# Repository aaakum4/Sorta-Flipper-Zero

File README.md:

# Sorta-Flipper-Zero by aaakum4 (Jake)

At the cost of a flipper zero, I thought that I may never own one. Then I found a hackster.io page that went through a full DIY and cheap Flipper Zero and I thought I'd try it myself with some changes. With this project, I should also learn a ton about PCB's and how electronics work.

V1 is a modular based project to ensure that it will work as planned, then, , I will completely custom make it for V2. 

Features: 
- Bluetooth Low Energy (BLE)
- Sub-GHz RF support (433 MHz)
- NFC / RFID functionality
- Infrared (IR) transmit and receive
- On-device display
- Physical navigation and action buttons
- Audible feedback via buzzer
- MicroSD card storage
- USB-C connectivity
- External antenna support

Not included (compared to a standard Flipper): 
- iButton / 1-Wire support - Capacitive touch input
- Internal battery charging and management
- Integrated antennas
- Fully enclosed, consumer-ready housing (I will make one for v2)

## Step 1 - Looking at the Flipper Zero Hardware

Before starting this project, I went through the Flipper Zero hardware documentation to understand how the device is built and what components it uses.

https://docs.flipper.net/zero/development/hardware/tech-specs
https://docs.flipper.net/zero/development/hardware/schematic

From this, I created the table below listing the main hardware blocks used in the Flipper Zero.
This table is used as a reference to understand the system, not something to copy directly.

### Flipper Zero – Hardware Component Overview

### Simplifying the Design (v1)
To keep the first version realistic and achievable, a few things were intentionally simplified.

#### USB Power Only
The device is powered only through USB, with no internal rechargeable battery.
This removes a lot of complexity around battery charging and safety, and makes early testing much easier. Portability isn’t the focus for the first version.

#### BLE Using a Module or Dev Board
Instead of designing a full BLE RF circuit, this project uses either an STM32WB5MMG module or a NUCLEO-WB55RG during early development.
This avoids antenna tuning issues and lets me focus more on firmware and overall system behaviour.

#### Simpler Sub-1 GHz Antenna
The Flipper Zero uses an antenna multiplexer to optimise different Sub-1 GHz bands. For this project, that part is left out.
A single antenna is used instead, which means reduced range, but much simpler hardware and easier bring-up.

#### Physical Reset Button
Rather than copying the Flipper Zero’s reset button combination logic, this design uses a dedicated reset button.
This keeps the schematic simpler and is more practical while debugging.

## Step 2 - v1 Hardware Selection (Module Based)
Based on the Flipper Zero reference design and the simplifications outlined above, the following components were chosen for the v1 module-based prototype.
This list reflects what will actually be used in the first working version of the project.

V1 - Selected Components:

## Step 3 – Schematic Design

With the overall architecture defined, I moved on to creating the full schematic in KiCad. The goal at this stage was to produce a complete, electrically correct design that could realistically be turned into a PCB, while still keeping the project modular and easy to iterate on.

I started by placing the STM32WB5MMGH6TR module and wiring all required power pins according to ST’s reference designs. This included separating the digital and analog supplies, tying VREF+ to VDDA, and correctly handling VBAT and VDDUSB. Decoupling capacitors were added close to each supply pin to ensure stable operation.

Next, the power system was designed around USB-C input. A main 3.3 V rail powers the MCU and core logic, while a second 3.3 V rail is used for external peripherals. 

Peripheral interfaces were then added. Instead of hard-coding specific modules, generic headers were used for NFC, Sub-1 GHz RF, display, IR, vibration, and expansion. These headers are labeled to match common module pinouts, allowing different breakout boards to be tested without changing the core design. Shared buses like SPI were carefully routed with separate chip-select signals.

Finally, the schematic was cleaned up and checked for electrical correctness. ERC warnings were addressed, unused pins were left intentionally for future use, and the design was reviewed to ensure it matched the original goals of being practical, modular, and suitable for a first hardware revision.

This step, to be honest, was kinda cooked. I went in a bit over my head with this and it took wayyyy longer than I had hoped and probably needed.

## Step 4 - Schematic fixes and cleanup

After the initial schematic was complete, I spent time going back through it to fix a number of electrical and structural issues flagged by ERC. This step was mainly about correcting mistakes rather than adding new features.

Most of the changes were around power domains, making sure VDD, VDDA, VREF+, VBAT, and VDDUSB were connected correctly and matched the STM32WB module datasheet. I cleaned up grounding, added and adjusted local decoupling capacitors, and removed a few incorrect connections that were previously masking ERC errors instead of solving them properly.

I also fixed the Bluetooth RF path, reworking the RF_OUT pin so it is routed through a DC-blocking capacitor to a u.FL connector. This replaces earlier incorrect handling of the RF pin and makes the onboard BLE functionality usable while keeping the design clean and standards-compliant.

This is an amazing sight, no ERC errors 🙏🏻

## Step 5 - Sorting and routing the board

I am now a new man...

This was my third time routing a PCB, and it was a mix of improvement… and pain. The Xiao MCU I used for the Macropad and the ESP32-S3-WROOM-1u for the development board don’t come close to the challenge I just faced. The STM32WB5MMG is tiny but packed with pins, making it a real test of patience. That said, I’m finally done, and I couldn’t be happier.

There were multiple reroutes along the way, mostly caused by pin congestion around the MCU and the sheer number of external connectors. Some compromises were necessary, like tighter clearances and smaller vias, but in the end, the board reached a fully routable and manufacturable state.

While it’s not perfect, this routing pass made me really proud of how far I’ve come since the Macropad project. It was a clear reminder that schematics are the easy part—routing is where designs are truly made or broken.

For this project, I worked with a 4-layer board (my first board over 2 layers) to manage density and RF performance, especially around the RF/Bluetooth section. I created a dedicated antenna keep-out zone to avoid copper interference, routed USB D+ and D− as a matched, parallel pair to maintain signal integrity, and widened power traces to 0.5 mm to reduce voltage drop.

Given the tight board size, I had to selectively use smaller vias and reduced trace widths in congested areas to complete the routing without violating design rules. To make assembly easier, I also added silkscreen boxes around each functional module, improving clarity and helping with placement. Looking back, having dedicated GND and +3.3 V layers definitely made this step much more manageable compared to what it would’ve been without them.

### The board

Size: 125mm x 70mm (quite alot bulkier than a normal flipper, I have no clue how they do it)
Vias:
1) Defult: 0.6 x 0.3
2) Smaller (Due to cramped space): 0.45 x 0.2
Routes:
1) Defult: Clearance = 0.2, Width = 0.2
2) Power: Clearance = 0.2, Width = 0.5
3) Smaller: Clearance = 0.2, Width = 0.15

#### Layer 1:

#### Layer 2: GND

#### Layer 3: +3V3

#### Layer 4:

#### 3D:

Estimated Time:
~2 hours of planning & component placement
~6 to 8 hours of routing + rerouting
~2 to 3 hours of cleanup, checks, and second-guessing everything

(Plus bonus time staring at the screen being stupid)

## Step ??? - Spontaneous Micro Project

For v2 of the Sorta Flipper Zero, I’ll most likely need to make a copper trace antenna for the NFC. For V1, I’m using a module, but I didn’t want to jump into V2 blindly. I decided to spend some time understanding how the module works, what I can bridge across, and even built my own small NFC card as an introduction to what I’ll need to do in V2.

Here’s the datasheet for the NFC module I hope to use: ST X-NUCLEO-NFC08A1

One thing I quickly noticed is that the antenna matters a lot. The orientation, size, and shape of the coil strongly affect the read range, and even small changes in trace layout or nearby copper can weaken the signal. This made it clear that designing a custom antenna will require careful attention.

I also learned that matching the antenna to the module is critical. The module expects the antenna to have roughly the right inductance; otherwise, communication becomes unreliable. Experimenting with the card showed me how adding or removing a turn in the coil noticeably changes performance.

Using the module is convenient because it handles much of the tuning internally. But seeing it in action made it obvious that if I want a custom copper trace for V2, I’ll need to account for these details myself.

This is the PCB I made from a simple schematic. I originally included an LED, but removed it in the PCB for the sake of readability and clarity. The file is in its own folder.

#### PCB:

#### 3D:

This step is not nesassary at all, but I truly found it really helpful with general understanding of this concept and I think it will be even more helpful when I make v2.

## Parts
Since alot of this iteration will be using modules there isn't that much soldering. Here is the parts list from JLCPCB PCBA.

## Firmware

Generating OTP Data (Flipper Zero)

This project uses the Flipper Zero firmware OTP generation script (scripts/otp.py) derived from the official Flipper Zero firmware repository (licensed under GPL-3.0) to generate device-specific OTP data.

### Example:

```
cd flipperzero-firmware/scripts

./otp.py generate \
  --version $((0x0c)) \
  --firmware $((0x07)) \
  --body $((0x09)) \
  --connect $((0x06)) \
  --display "mgg" \
  --color "transparent" \
  --region "world" \
  --name "Greg" \
  myotp
```

**Warning**: OTP memory is one-time programmable.
Flashing incorrect data may permanently affect the device.

### Installing Firmware via qFlipper

https://github.com/flipperdevices/qFlipper.git
Firmware installation is performed using qFlipper, the official Flipper Zero desktop application.

1. Install qFlipper from the official Flipper Zero website
2. Connect the device via USB
3. Select the appropriate firmware package
4. Follow on-screen flashing instructions

This project may reference prebuilt firmware or OTP data derived from the Flipper Zero firmware repository. All such components remain licensed under GPL-3.0, and source code is provided in accordance with that license.

## ⚠️ Problem solving

The NFC chip used on the X‑NUCLEO expansion board is the ST25R3916B, which has a different IC identity value to the ST25R3916 used in the Flipper Zero. Although the two chips share the same register map and functionality, the firmware performs an identity check during initialisation, causing the driver to fail when the B variant is detected.

To resolve this, I forked the official Flipper Zero firmware repository (https://github.com/flipperdevices/flipperzero-firmware) and modified the NFC driver to accept the ST25R3916B IC identity. This allows the existing firmware to operate correctly with the alternative NFC hardware without affecting functionality.

The modified source code is available here:
https://github.com/aaakum4/flipperzero-firmware.git

## License

This project is licensed under the GNU General Public License v3.0 (GPL-3.0).

This project includes and is derived from code from:
- flipperzero-firmware by skotopes (Top contributor)
  Licensed under GPL-3.0

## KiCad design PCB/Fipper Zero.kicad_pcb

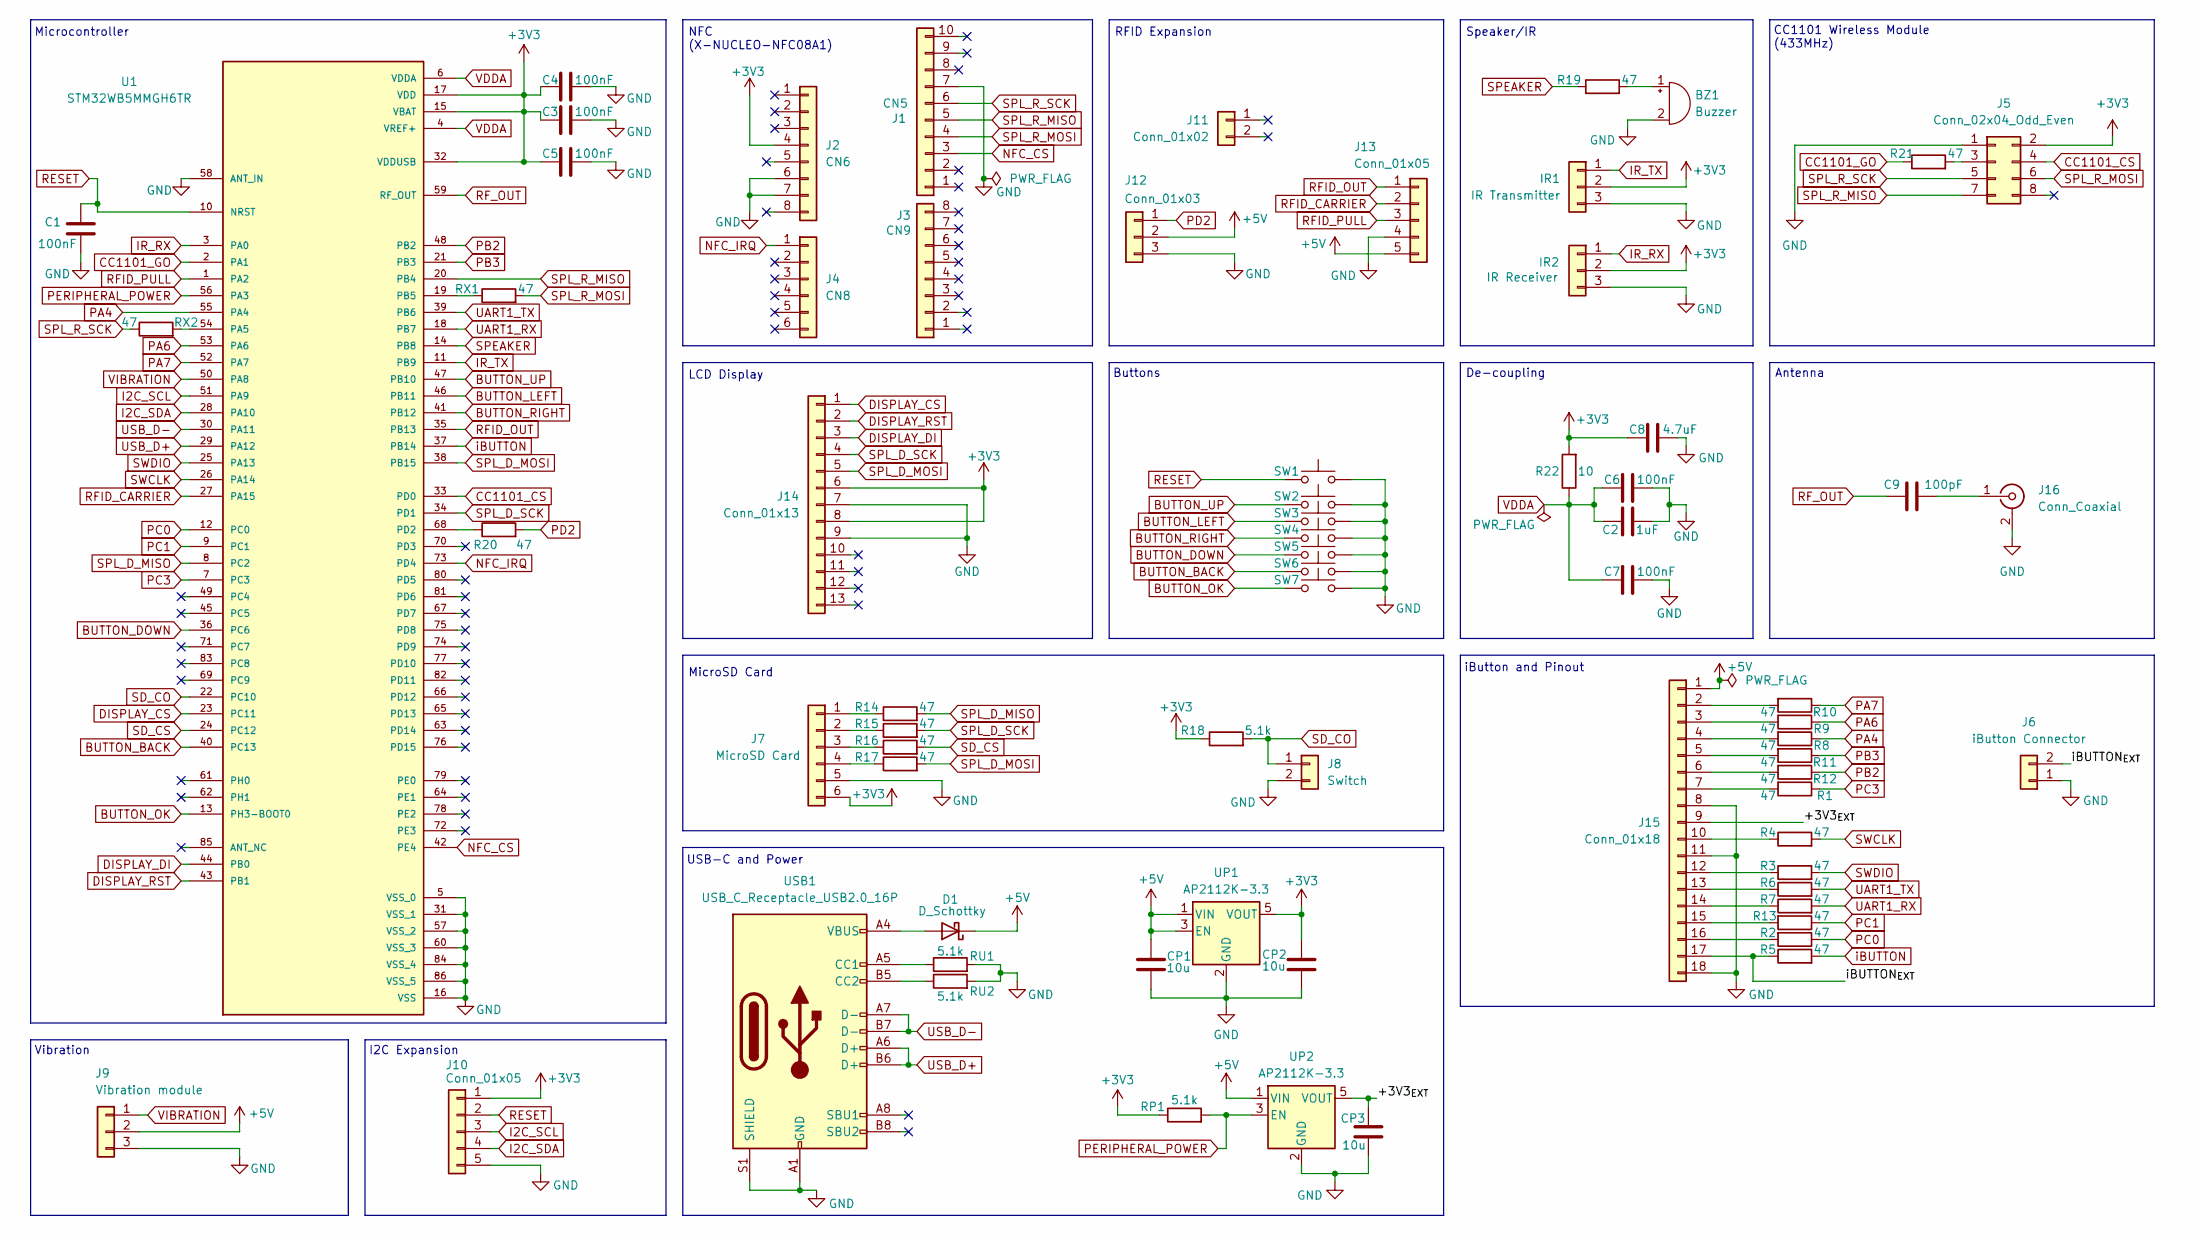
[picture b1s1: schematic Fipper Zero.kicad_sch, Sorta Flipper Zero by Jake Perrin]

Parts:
BZ1: Buzzer; BUZ-TH_BD9.0-P4.00-D0.6-FD
C1, C3, C4, C5, C6, C7: 100nF; C_0603_1608Metric
C2: 1uF; C_0603_1608Metric
C8: 4.7uF; C_0805_2012Metric
C9: 100pF; C_0402_1005Metric
CP1, CP2, CP3: 10u; C_0805_2012Metric
D1: D_Schottky; D_SOD-123
IR1: IR Transmitter; PinHeader_1x03_P2.54mm_Vertical
IR2: IR Receiver; PinHeader_1x03_P2.54mm_Vertical
J1: CN5; PinHeader_1x10_P2.54mm_Vertical
J2: CN6; PinHeader_1x08_P2.54mm_Vertical
J3: CN9; PinHeader_1x08_P2.54mm_Vertical
J4: CN8; PinHeader_1x06_P2.54mm_Vertical
J5: Conn_02x04_Odd_Even; PinHeader_2x04_P2.54mm_Vertical
J6: iButton Connector; PinHeader_1x02_P2.54mm_Vertical
J7: MicroSD Card; PinHeader_1x06_P2.54mm_Vertical
J8: Switch; PinHeader_1x02_P2.54mm_Vertical
J9: Vibration module; PinHeader_1x02_P2.54mm_Vertical
J10, J13: Conn_01x05; PinHeader_1x05_P2.54mm_Vertical
J11: Conn_01x02; PinHeader_1x02_P2.54mm_Vertical
J12: Conn_01x03; PinHeader_1x03_P2.54mm_Vertical
J14: Conn_01x13; PinHeader_1x13_P2.54mm_Vertical
J15: Conn_01x18; PinHeader_1x18_P2.54mm_Vertical
J16: Conn_Coaxial; U.FL_Hirose_U.FL-R-SMT-1_Vertical
R1, R2, R3, R4, R5, R6, R7, R8, R9, R10, R11, R12, R13, R14, R15, R16, R17, R19, R20, R21: 47; R_0603_1608Metric
R18: 5.1k; R_0603_1608Metric
R22: 10; R_0603_1608Metric
RP1: 5.1k; R_0603_1608Metric
RU1, RU2: 5.1k; R_0603_1608Metric
RX1, RX2: 47; R_0603_1608Metric
SW1, SW2, SW3, SW4, SW5, SW6, SW7: SW_Push; SW_PUSH_6mm
U1: STM32WB5MMGH6TR; LCC-LGA-86_L11.0-W7.3_STM32WB5MMGH6TR; PARTREV 8
UP1, UP2: AP2112K-3.3; SOT-23-5
USB1: USB_C_Receptacle_USB2.0_16P; USB_C_Receptacle_HRO_TYPE-C-31-M-12

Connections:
+3V3: C3.1, C4.1, C5.1, C8.1, CP2.1, IR1.2, IR2.2, J2.4, J5.2, J7.6, J10.1, J14.6, J14.8, R18.1, R22.2, RP1.1, U1.15 (VBAT), U1.17 (VDD), U1.32 (VDDUSB), UP1.5 (VOUT)
+5V: CP1.1, D1.1 (K), J9.2, J12.2, J13.5, J15.1, UP1.1 (VIN), UP1.3 (EN), UP2.1 (VIN)
/+3V3_{EXT}: CP3.1, J15.9, UP2.5 (VOUT)
/iBUTTON_{EXT}: J6.2, J15.17, R5.1
BUTTON_BACK: SW6.1, U1.40 (PC13)
BUTTON_DOWN: SW5.1, U1.36 (PC6)
BUTTON_LEFT: SW3.1, U1.46 (PB11)
BUTTON_OK: SW7.1, U1.13 (PH3-BOOT0)
BUTTON_RIGHT: SW4.1, U1.41 (PB12)
BUTTON_UP: SW2.1, U1.47 (PB10)
CC1101_CS: J5.4, U1.33 (PD0)
CC1101_GO: R21.1, U1.2 (PA1)
DISPLAY_CS: J14.1, U1.23 (PC11)
DISPLAY_DI: J14.3, U1.44 (PB0)
DISPLAY_RST: J14.2, U1.43 (PB1)
GND: BZ1.2 (-), C1.2, C2.2, C3.2, C4.2, C5.2, C6.2, C7.2, C8.2, CP1.2, CP2.2, CP3.2, IR1.3, IR2.3, J1.7, J2.6, J2.7, J5.1, J6.1, J7.5, J8.2, J9.3, J10.5, J12.3, J13.4, J14.7, J14.9, J15.8, J15.11, J15.18, J16.2 (Ext), RU1.2, RU2.2, SW1.2, SW2.2, SW3.2, SW4.2, SW5.2, SW6.2, SW7.2, U1.5 (VSS_0), U1.16 (VSS), U1.31 (VSS_1), U1.57 (VSS_2), U1.58 (ANT_IN), U1.60 (VSS_3), U1.84 (VSS_4), U1.86 (VSS_5), UP1.2 (GND), UP2.2 (GND), USB1.A1 (GND), USB1.A12 (GND), USB1.B1 (GND), USB1.B12 (GND), USB1.S1 (SHIELD)
I2C_SCL: J10.3, U1.51 (PA9)
I2C_SDA: J10.4, U1.28 (PA10)
IR_RX: IR2.1, U1.3 (PA0)
IR_TX: IR1.1, U1.11 (PB9)
NFC_CS: J1.3, U1.42 (PE4)
NFC_IRQ: J4.1, U1.73 (PD4)
unnamed: BZ1.1 (+), R19.2
unnamed: D1.2 (A), USB1.A4 (VBUS), USB1.A9 (VBUS), USB1.B4 (VBUS), USB1.B9 (VBUS)
unnamed: J5.3, R21.2
unnamed: J7.1, R14.1
unnamed: J7.2, R15.1
unnamed: J7.3, R16.1
unnamed: J7.4, R17.1
unnamed: J15.2, R10.2
unnamed: J15.3, R9.2
unnamed: J15.4, R8.2
unnamed: J15.5, R11.2
unnamed: J15.6, R12.2
unnamed: J15.7, R1.2
unnamed: J15.10, R4.1
unnamed: J15.12, R3.1
unnamed: J15.13, R6.1
unnamed: J15.14, R7.1
unnamed: J15.15, R13.2
unnamed: J15.16, R2.2
unnamed 41: C9.2, J16.1 (In); also elsewhere on the board
unnamed: RX2.2, U1.54 (PA5)
unnamed: RX1.1, U1.19 (PB5)
unnamed: R20.1, U1.68 (PD2)
unnamed: RU1.1, USB1.A5 (CC1)
unnamed: RU2.1, USB1.B5 (CC2)
PA4: R8.1, U1.55 (PA4)
PA6: R9.1, U1.53 (PA6)
PA7: R10.1, U1.52 (PA7)
PB2: R12.1, U1.48 (PB2)
PB3: R11.1, U1.21 (PB3)
PC0: R2.1, U1.12 (PC0)
PC1: R13.1, U1.9 (PC1)
PC3: R1.1, U1.7 (PC3)
PD2: J12.1, R20.2
PERIPHERAL_POWER: RP1.2, U1.56 (PA3), UP2.3 (EN)
RESET: C1.1, J10.2, SW1.1, U1.10 (NRST)
RFID_CARRIER: J13.2, U1.27 (PA15)
RFID_OUT: J13.1, U1.35 (PB13)
RFID_PULL: J13.3, U1.1 (PA2)
RF_OUT: C9.1, U1.59 (RF_OUT); also elsewhere on the board
SD_CO: J8.1, R18.2, U1.22 (PC10)
SD_CS: R16.2, U1.24 (PC12)
SPEAKER: R19.1, U1.14 (PB8)
SPL_D_MISO: R14.2, U1.8 (PC2)
SPL_D_MOSI: J14.5, R17.2, U1.38 (PB15)
SPL_D_SCK: J14.4, R15.2, U1.34 (PD1)
SPL_R_MISO: J1.5, J5.7, U1.20 (PB4)
SPL_R_MOSI: J1.4, J5.6, RX1.2
SPL_R_SCK: J1.6, J5.5, RX2.1
SWCLK: R4.2, U1.26 (PA14)
SWDIO: R3.2, U1.25 (PA13)
UART1_RX: R7.2, U1.18 (PB7)
UART1_TX: R6.2, U1.39 (PB6)
USB_D+: U1.29 (PA12), USB1.A6 (D+), USB1.B6 (D+)
USB_D-: U1.30 (PA11), USB1.A7 (D-), USB1.B7 (D-)
VDDA: C2.1, C6.1, C7.1, R22.1, U1.4 (VREF+), U1.6 (VDDA)
VIBRATION: J9.1, U1.50 (PA8)
iBUTTON: R5.2, U1.37 (PB14)

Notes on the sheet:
De-coupling
Buttons
MicroSD Card
CC1101 Wireless Module (433MHz)
NFC (X-NUCLEO-NFC08A1)
LCD Display
USB-C and Power
iButton and Pinout
Speaker/IR
Microcontroller
I2C Expansion
Vibration
RFID Expansion
Antenna

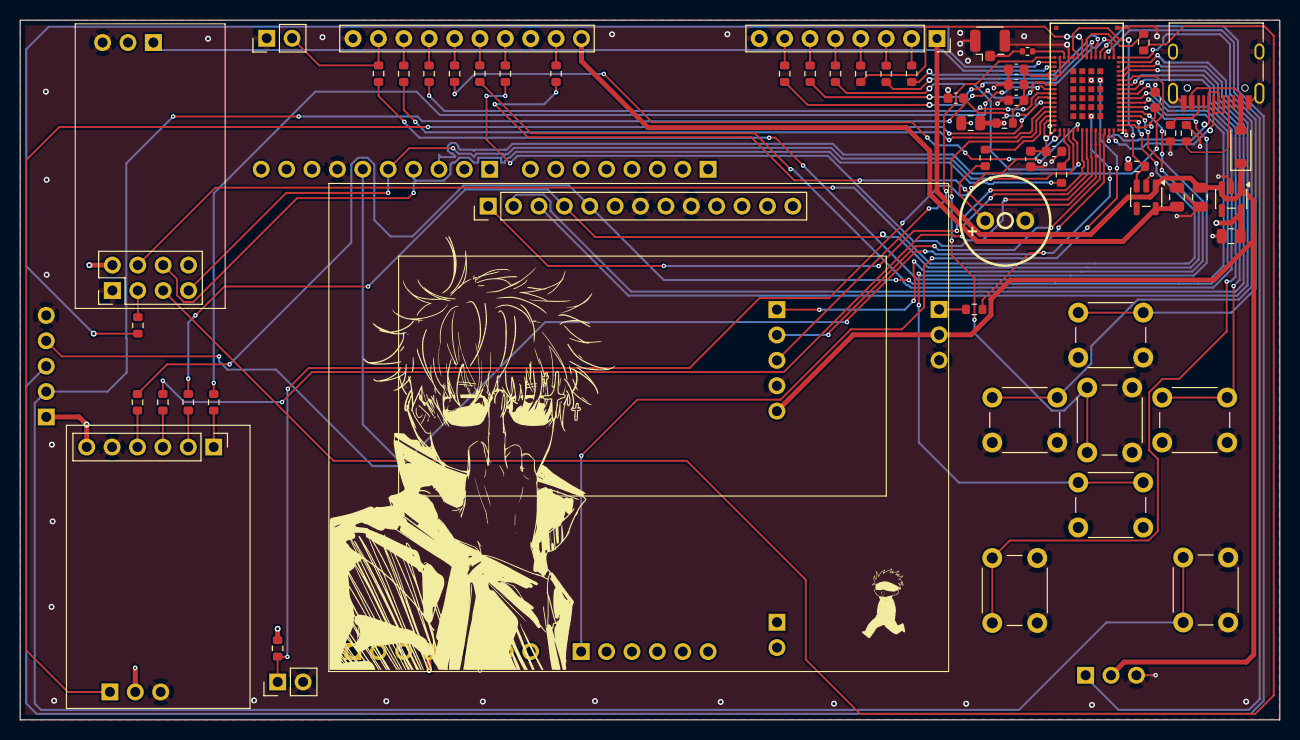
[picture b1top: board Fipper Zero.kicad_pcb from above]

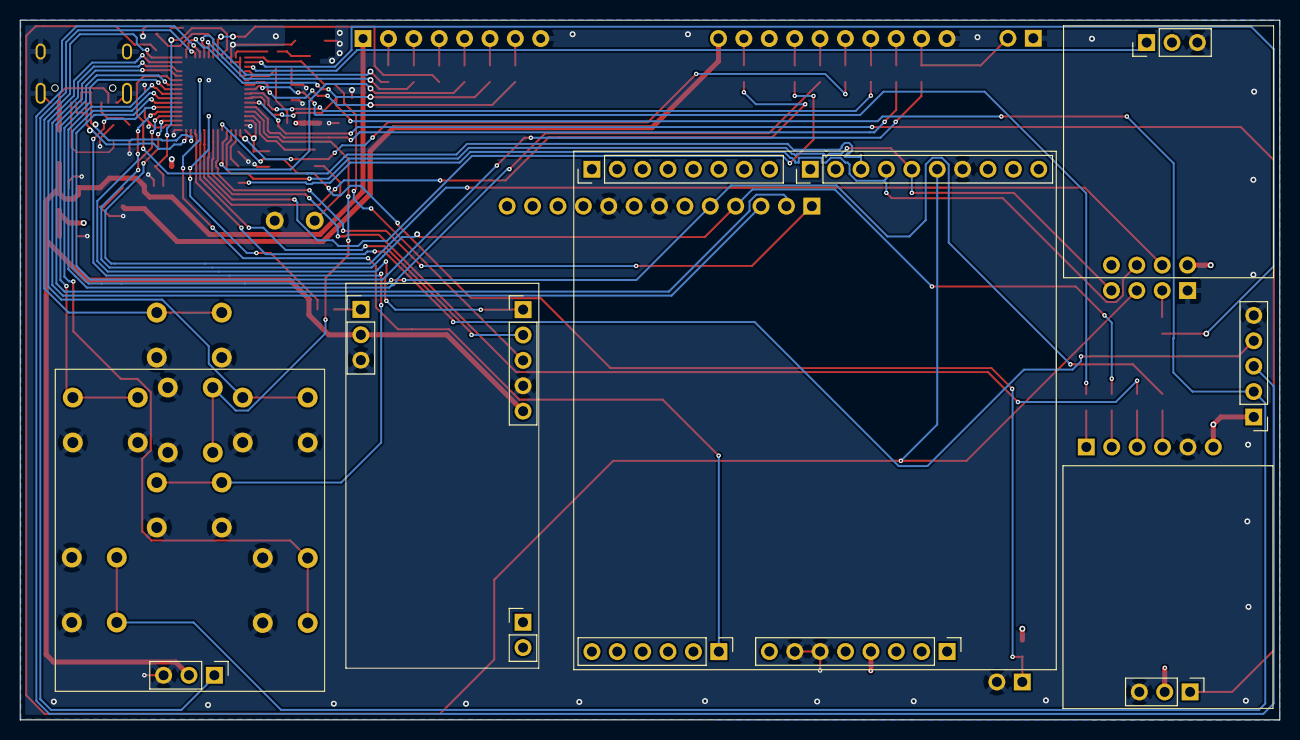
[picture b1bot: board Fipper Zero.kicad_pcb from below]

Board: 4 copper layers, 126.0 x 70.0 mm, 70 parts (11 on the bottom side), 80 nets.

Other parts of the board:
R23: 0; R_0402_1005Metric

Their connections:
unnamed 41: R23.2; also elsewhere on the board
RF_OUT: R23.1; also elsewhere on the board

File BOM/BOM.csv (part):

JLCPCB BOM Tool - BOM Matching,,,,,,,,,,,,,,,,,
BOM name：Fipper Zero-JLCPCB Assembly Order.xlsx,,,Download Time：2025-12-26 21:10:08,,,,"* Our matching results are updated in real-time, but stock and prices may change. 
If it's been over 24 hours, please re-match before placing your order.",,,,,,,,,,
PCB Assembled Qty：5,,,Est. Total Price：65.3443,,,,,,,,,,,,,,
Your BOM,,,,,Matched Parts,,,,,,,Order Information,,,,,
Top Designator,Bottom Designator,Comment,Footprint,JLCPCB Part #,Matches,Part # ,Manufacturer,Footprint,Description,Category,Warning,JLCPCB Part #,Product link,Lib Type,Qty,Source,Total Price ($)
BZ1,,Buzzer,BUZ-TH_BD9.0-P4.00-D0.6-FD,,Select by Customer,QMB-09B-03,Jiangsu Huaneng Elec,"插件,D=9mm","-20℃~+70℃ 2.7kHz 2V~5V 3V 5.7mm 50mA 85dB 9mm Electromagnetic Passive (Externally Driven) Plugin,D=9mm Buzzers ROHS",Buzzers,,C96256,https://jlcpcb.com/partdetail/Jiangsu_HuanengElec-QMB_09B03/C96256,Extended,6,6 JLCPCB,0.6714
C2,,1uF,C_0603_1608Metric,,Select by Customer,CL10A105KA8NNNC,Samsung Electro-Mechanics,0603,1uF 25V X5R ±10% 0603 Multilayer Ceramic Capacitors MLCC - SMD/SMT ROHS,Multilayer Ceramic Capacitors MLCC - SMD/SMT,,C5673,https://jlcpcb.com/partdetail/6132-CL10A105KA8NNNC/C5673,Extended,20,20 JLCPCB,0.086
"C4,C5,C7,C6,C3,C1",,100nF,C_0603_1608Metric,,Select by Customer,CL10B104KA8NNNC,Samsung Electro-Mechanics,0603,100nF 25V X7R ±10% 0603 Multilayer Ceramic Capacitors MLCC - SMD/SMT ROHS,Multilayer Ceramic Capacitors MLCC - SMD/SMT,,C1590,https://jlcpcb.com/partdetail/1942-CL10B104KA8NNNC/C1590,Extended,40,40 JLCPCB,0.132
C8,,4.7uF,C_0805_2012Metric,,Select by Customer,CL21A475KOFNNNE,Samsung Electro-Mechanics,0805,16V 4.7uF X5R ±10% 0805 Multilayer Ceramic Capacitors MLCC - SMD/SMT ROHS,Multilayer Ceramic Capacitors MLCC - SMD/SMT,,C1746,https://jlcpcb.com/partdetail/2098-CL21A475KOFNNNE/C1746,Extended,20,20 JLCPCB,0.288
"CP3,CP1,CP2",,10u,C_0805_2012Metric,,Select by Customer,CL21A106KAYNNNE,Samsung Electro-Mechanics,0805,10uF 25V X5R ±10% 0805 Multilayer Ceramic Capacitors MLCC - SMD/SMT ROHS,Multilayer Ceramic Capacitors MLCC - SMD/SMT,,C15850,https://jlcpcb.com/partdetail/16532-CL21A106KAYNNNE/C15850,Basic,25,25 JLCPCB,0.2475
D1,,D_Schottky,D_SOD-123,,Select by Customer,SS14,MDD(Microdiode Semiconductor),SMA(DO-214AC),-55℃~+150℃ 1A 25A 300uA@40V 40V 550mV@1A Independent SMA(DO-214AC) Schottky Diodes ROHS,Schottky Diodes,,C2480,https://jlcpcb.com/partdetail/MDD_Microdiode_Semiconductor-S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,Basic,15,15 JLCPCB,0.2265
J5,,Conn_02x04_Odd_Even,PinHeader_2x04_P2.54mm_Vertical,,Select by Customer,2.54-1*40P直针,BOOMELE(Boom Precision Elec),"插件,P=2.54mm","-25℃~+85℃ 1 1x40P 2.54mm 2.5mm 3A 3mm 40P 6mm Black Brass Gold Pin Header Through Hole Plugin,P=2.54mm Pin Headers ROHS",Pin Headers,1.Multiple lines in the BOM have been matched to the same part. Please check if the matching is correct. ;,C2337,https://jlcpcb.com/partdetail/2712-2_54_1_40P/C2337,Extended,0,0 JLCPCB,0
J6,,iButtonConnector,PinHeader_1x02_P2.54mm_Vertical,,Select by Customer,2.54-1*40P直针,BOOMELE(Boom Precision Elec),"插件,P=2.54mm","-25℃~+85℃ 1 1x40P 2.54mm 2.5mm 3A 3mm 40P 6mm Black Brass Gold Pin Header Through Hole Plugin,P=2.54mm Pin Headers ROHS",Pin Headers,1.Multiple lines in the BOM have been matched to the same part. Please check if the matching is correct. ;,C2337,https://jlcpcb.com/partdetail/2712-2_54_1_40P/C2337,Extended,0,0 JLCPCB,0
J7,,MicroSDCard,PinHeader_1x06_P2.54mm_Vertical,,Select by Customer,2.54-1*40P直针,BOOMELE(Boom Precision Elec),"插件,P=2.54mm","-25℃~+85℃ 1 1x40P 2.54mm 2.5mm 3A 3mm 40P 6mm Black Brass Gold Pin Header Through Hole Plugin,P=2.54mm Pin Headers ROHS",Pin Headers,1.Multiple lines in the BOM have been matched to the same part. Please check if the matching is correct. ;,C2337,https://jlcpcb.com/partdetail/2712-2_54_1_40P/C2337,Extended,0,0 JLCPCB,0
J8,,Switch,PinHeader_1x02_P2.54mm_Vertical,,Select by Customer,2.54-1*40P直针,BOOMELE(Boom Precision Elec),"插件,P=2.54mm","-25℃~+85℃ 1 1x40P 2.54mm 2.5mm 3A 3mm 40P 6mm Black Brass Gold Pin Header Through Hole Plugin,P=2.54mm Pin Headers ROHS",Pin Headers,"1.The comment (2.54-1*40P直针) of this part does not match the one (Switch) provided in your BOM. Please confirm;
2.Multiple lines in the BOM have been matched to the same part. Please check if the matching is correct. ;",C2337,https://jlcpcb.com/partdetail/2712-2_54_1_40P/C2337,Extended,0,0 JLCPCB,0
J14,,Conn_01x13,PinHeader_1x13_P2.54mm_Vertical,,Select by Customer,2.54-1*40P直针,BOOMELE(Boom Precision Elec),"插件,P=2.54mm","-25℃~+85℃ 1 1x40P 2.54mm 2.5mm 3A 3mm 40P 6mm Black Brass Gold Pin Header Through Hole Plugin,P=2.54mm Pin Headers ROHS",Pin Headers,1.Multiple lines in the BOM have been matched to the same part. Please check if the matching is correct. ;,C2337,https://jlcpcb.com/partdetail/2712-2_54_1_40P/C2337,Extended,0,0 JLCPCB,0
J15,,Conn_01x18,Flipper_Zero_Straight,,Select by Customer,2.54-1*40P直针,BOOMELE(Boom Precision Elec),"插件,P=2.54mm","-25℃~+85℃ 1 1x40P 2.54mm 2.5mm 3A 3mm 40P 6mm Black Brass Gold Pin Header Through Hole Plugin,P=2.54mm Pin Headers ROHS",Pin Headers,1.Multiple lines in the BOM have been matched to the same part. Please check if the matching is correct. ;,C2337,https://jlcpcb.com/partdetail/2712-2_54_1_40P/C2337,Extended,0,0 JLCPCB,0
J16,,Conn_Coaxial,U.FL_Hirose_U.FL-R-SMT-1_Vertical,,Select by Customer,U.FL-R-SMT-1(10),HRS(Hirose),SMD,-40℃~+90℃ 1 1.25mm 2mm 50Ω 6GHz Board Side IPEX Male Pin SMD Coaxial Connectors (RF) ROHS,Coaxial Connectors (RF),,C88373,https://jlcpcb.com/partdetail/HRS_Hirose-U_FL_R_SMT_1_10/C88373,Extended,5,5 JLCPCB,0.947
"R17,RX1,R7,R12,R4,R5,R19,R6,R10,R9,R8,R2,R14,R3,RX2,R13,R16,R21,R15,R20,R11,R1",,47,R_0603_1608Metric,,Select by Customer,GZ1608D601TF,Sunlord,0603,-55℃~+125℃ 1 200mA 450mΩ 600Ω@100MHz ±25% 0603 Ferrite Beads ROHS,Ferrite Beads,"1.The comment (GZ1608D601TF) of this part does not match the one (47) provided in your BOM. Please confirm;
2.There may be multiple types of parts, but one type of part has been matched. Please check.;",C1002,https://jlcpcb.com/partdetail/Sunlord-GZ1608D601TF/C1002,Basic,116,116 JLCPCB,0.7772
"R18,RU2,RU1,RP1",,5.1k,R_0603_1608Metric,,Select by Customer,0402WGF5101TCE,UNI-ROYAL(Uniroyal Elec),0402,-55℃~+155℃ 5.1kΩ 50V 62.5mW Thick Film Resistor ±1% ±100ppm/℃ 0402 Chip Resistor - Surface Mount ROHS,Chip Resistor - Surface Mount,"1.The comment (0402WGF5101TCE) of this part does not match the one (5.1k) provided in your BOM. Please confirm;
2.There may be multiple types of parts, but one type of part has been matched. Please check.;",C25905,https://jlcpcb.com/partdetail/26648-0402WGF5101TCE/C25905,Basic,30,30 JLCPCB,0.015
R22,,10,R_0603_1608Metric,,Select by Customer,0603WAF100JT5E,UNI-ROYAL(Uniroyal Elec),0603,-55℃~+155℃ 100mW 10Ω 75V Thick Film Resistor ±1% ±400ppm/℃ 0603 Chip Resistor - Surface Mount ROHS,Chip Resistor - Surface Mount,1.The comment (0603WAF100JT5E) of this part does not match the one (10) provided in your BOM. Please confirm;,C22859,https://jlcpcb.com/partdetail/23586-0603WAF100JT5E/C22859,Basic,20,20 JLCPCB,0.02
R23,,0,R_0402_1005Metric,,Select by Customer,PA0402-R-070RL,YAGEO,0402,-55℃~+125℃ 0Ω 62.5mW ±150ppm/℃ 0402 Chip Resistor - Surface Mount ROHS,Chip Resistor - Surface Mount,,C4044221,https://jlcpcb.com/partdetail/YAGEO-PA0402_R070RL/C4044221,Extended,7,7 JLCPCB,0.9121
"SW4,SW5,SW1,SW3,SW7,SW6,SW2",,SW_Push,SW_PUSH_6mm,,Select by Customer,HX-6x6x7.3-TP FT square button,hanxia,"SMD,6x6mm","SMD,6x6mm Tactile Switches ROHS",,,C49234152,https://jlcpcb.com/partdetail/C49234152,Extended,35,35 JLCPCB,0.9765
U1,,STM32WB5MMGH6TR,LCC-LGA-86_L11.0-W7.3_STM32WB5MMGH6TR,,Select by Customer,STM32WB5MMGH6TR,STMicroelectronics,LFLGA-86,-40℃~+85℃ -96dBm 1.71V~3.6V 2.4GHz 2.4GHz~2.4835GHz 2Mbps 6dBm SPI ZigBee LFLGA-86 RF Transceiver ICs ROHS,RF Transceiver ICs,,C5184586,https://jlcpcb.com/partdetail/STMicroelectronics-STM32WB5MMG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,Extended,5,5 JLCPCB,58.108
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
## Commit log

2025-12-19 Enhance README with Flipper Zero hardware details
    Added an overview of the Flipper Zero hardware components.
2025-12-19 Enhance README with hardware overview and design notes
    Added detailed hardware component overview and design simplifications for the Flipper Zero project.
2025-12-19 Update Flipper Zero hardware component overview
2025-12-19 Fix image tag formatting in README.md
2025-12-20 Enhance README with images and hardware links
    Added images and links to Flipper Zero hardware documentation.
2025-12-20 Document schematic design process in README
    Added detailed explanation of the schematic design process, including power system and peripheral interfaces.
2025-12-20 Update README with detailed project overview
    Expanded project description to include learning goals and project iterations.
2025-12-22 Document schematic fixes and cleanup in README
    Updated the README to reflect schematic fixes and cleanup details.
2025-12-22 Enhance README with project overview and updates
    Updated README with detailed project steps and images.
2025-12-22 Update README with project features and limitations
    Added features and limitations of the DIY Flipper Zero project.
2025-12-22 Update README with hardware and schematic design steps
    Added sections on hardware overview and schematic design.
2025-12-22 Added v1.0 of the schematic
2025-12-24 Update README with sorting and routing notes
    Added notes on sorting and routing the board.
2025-12-24 Update PCB design notes in README
    Adjusted routing and via sizes for a compact PCB design.
2025-12-26 Update README with additional design notes
2025-12-26 Update README with layer headings and images
2025-12-26 Revise README with project updates and V2 plans
    Updated project description and added details about V2 development, including antenna considerations and PCB design.
2025-12-26 Add images and update hardware component overview
2025-12-26 NFC Micro Project Added
2025-12-26 Files
2026-01-14 Revise project title in README.md
    Updated project title and added author name.
2026-01-22 Update README to include license information
    Add license section and attribution to README.
2026-01-22 Fix spelling errors in README.md
    Corrected spelling errors and improved clarity in the README.
2026-01-22 Replace MIT License with GNU GPL v3
2026-01-22 Include third-party software notices
    Add third-party notices for flipperzero-firmware.
2026-01-22 Create otp.py
    Import scripts/otp.py from flipperzero-firmware (GPL-3.0)
2026-01-22 Add parts list section to README
    Added a parts list section with an image from JLCPCB PCBA.
2026-01-22 Update README with OTP generation and firmware details
    Added instructions for generating OTP data and firmware installation using qFlipper.
2026-01-22 Enhance Problem solving section in README
    Updated the Problem solving section to include a warning icon and clarified the NFC chip differences and firmware modifications.
2026-01-22 Add qFlipper GitHub link to README
2026-01-22 Add firmware repository link
